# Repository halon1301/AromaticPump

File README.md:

# M5 Blowover Pump

## This device may be used in ways which can be unsafe.  I take no responsibility for unsafe usage, be smart and think with the head on your shoulders, not between your legs.
## DO NOT USE THIS DEVICE ALONE
## DO NOT USE WITH VOLATILE COMPOUNDS
## DO NOT USE WHILE INTOXICATED

Now that I've got the safety stuff done, let's get on to the fun stuff.

### Full BOM

This BOM assumes you're using the provided circuit board designs, if you're going to use strip/protoboard to build this, 
you'll need to account for the differences

| Count | Part                                         | Supplier            | Link                                                                              |
|-------|----------------------------------------------|---------------------|-----------------------------------------------------------------------------------|
| 1     | Main Circuit Board                           | PCBWay              | n/a                                                                               |
| 1     | M5Stack Core 2                               | 	DigiKey            | https://www.digikey.ca/en/products/detail/m5stack-technology-co-ltd/K010/13151126 |
| 1     | Simple RF M4 315Mhz Momentary	               | Adafruit            | https://www.adafruit.com/product/1096                                             |
| 1     | 2 Button Key Fob	                            | Adafruit	           | https://www.adafruit.com/product/1391                                             |
| 1     | 4 Button Key Fob                             | 	Adafruit	          | https://www.adafruit.com/product/1095                                             |
| 1     | 12V Pump	                                    | Amazon	             | https://a.co/d/cortGed                                                            |
| 1     | 12V 2A Power Adapter	                        | Amazon	             | https://a.co/d/3SDBTkm                                                            |
| 1     | DRV8871 DC Motor Driver(Adafruit Brand)	     | Amazon or Adafruit	 | https://www.adafruit.com/product/3190                                             |
| 1     | 7-24V to 5V Buck Converter ( RB-Dfr-956)     | RobotShop	          | https://www.robotshop.com/products/dfrobot-dc-dc-buck-converter-7-24v-to-5v-4a    |
| 1     | Barrel Plug Adapter 5.5mm                    | Amazon              | https://a.co/d/0rlC4Ci                                                            |
| 3     | 10kOhm Resistors                             | Digikey             | https://www.digikey.ca/en/products/detail/yageo/CFR-25JB-52-10K/338               |
| 3     | 22kOhm Resistors                             | DigiKey             | https://www.digikey.ca/en/products/detail/yageo/CFR-25JB-52-22K/1306              |
| 1     | Some kind of physical latching on/off switch | Amazon              | https://a.co/d/hDef00k                                                            |
| 1     | Silicone Tubing                              | Amazon              | https://a.co/d/bUvRTfo                                                            |                                                          |
| 2     | Barb Through fitting                         | Amazon              | https://a.co/d/0NNg51N                                                            |
| 2     | FPC 30 Pin boards                            | Amazon              | https://a.co/d/jerJJ3a                                                                                  |
| 1| 30 Pin ribbon cable | Amazon | https://a.co/d/dCT5ZlU                                                            |

The 4 button fob is entirely optional, as it does the same things the touchscreen on the m5stack already does.  The 2 
button remote is for a sub to use, if you don't want this, consider it optional. Only button 2 is used on the 2 button 
remote (I use button 1 for a lube pump, so it's not wired up).

There are included PCB diagrams made in KiCAD, you can get them printed with PCBWay, but this whole project could easily
be made using proto/strip board and wires.

STLs for a case are also included, these however assume you are using the PCB included with the project, please remix 
and create your own for your use case!

### Assembly
All components are through hole, this is to keep it easy for people to make on their own with basic soldering skills, 
and without requiring special PCBs or other things that may be slightly more esoteric.

The designed PCB uses standard expansion pins for most things, the connectors for the switch and the 12v to the motor 
driver are designed to use a screw block, but you really could just solder wires into the hole and call it done.  Mounting 
points on the board are designed to use M3 screws, I'd recommend a nylon washer between the screw and the board, if you 
use inserts in your case, you should probably put something on the other side, but it's mostly because I'm paranoid 
about shorts.  In my design I use a pair of breakout boards and a 30p ribbon cable to lift the M5 stack off the board 
and give me nice clearance, once again, these are optional, you could do this however you want.

If your using the provided PCB design, you'll want to use some rosin flux, it'll make your life easier.  Solder 
everything to the board where labeled.

Don't connect your M5Stack to the board when you flash it, the USB 5v is not isolated from the 5v bus, and you'll get 
weird results, or fuck your computer up.

Bring up platformIO in your IDE of choice, and run the build, then upload to your board and you are good to plug it in. 
Power up the pump, and you're ready to go.

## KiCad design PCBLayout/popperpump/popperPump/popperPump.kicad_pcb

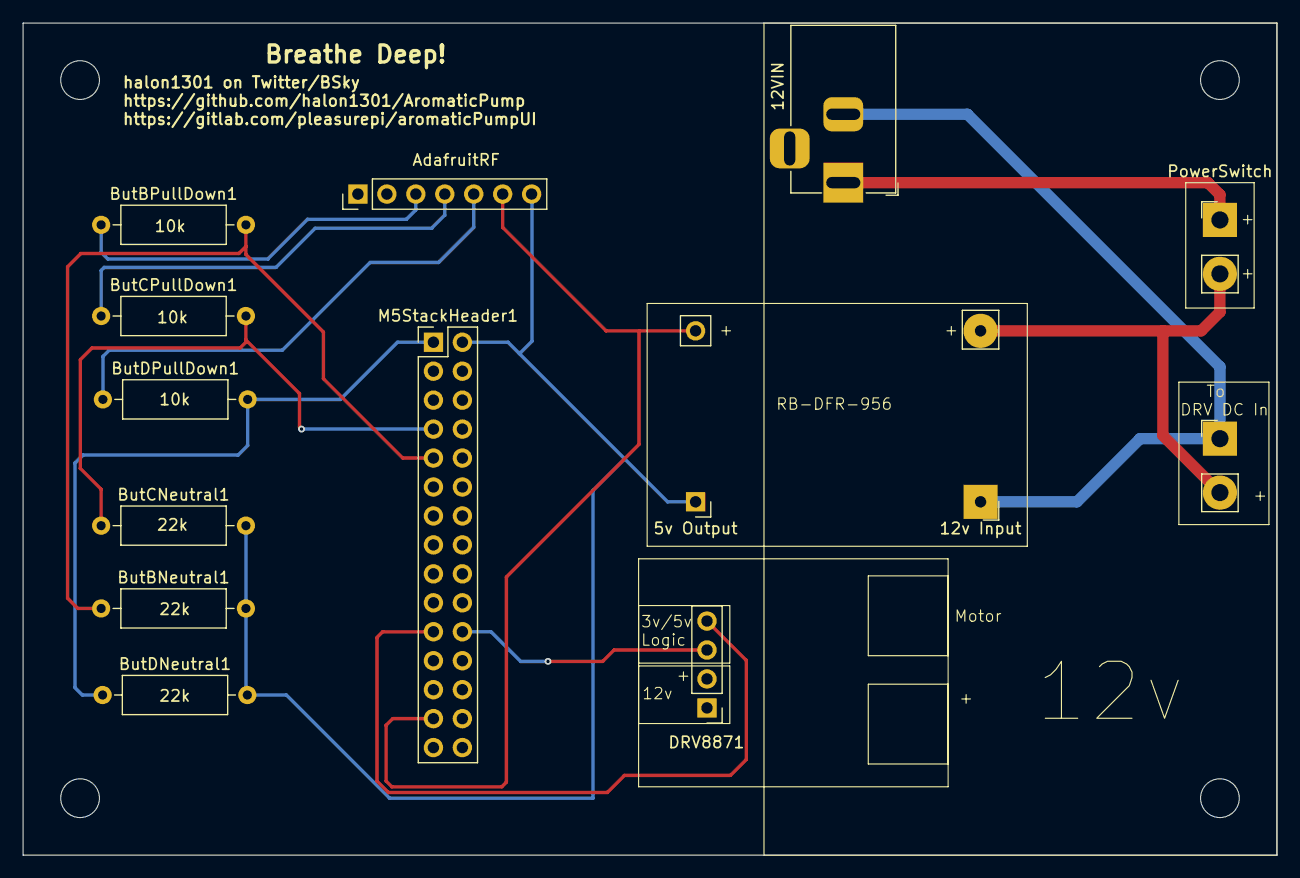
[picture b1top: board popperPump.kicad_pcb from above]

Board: 2 copper layers, 110.0 x 73.0 mm, 14 parts (0 on the bottom side), 10 nets.

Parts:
5v Output: RB-Dfr-956-5vout; PinHeader_1x02_P2.54mm_Vertical-BuckConverter-DFR-956
12VIN: Barrel_Jack; BarrelJack_Horizontal
12v Input: RB-Dfr-956-12vin; PinHeader_1x02_P2.54mm_Vertical-BuckConverter-DFR-956
AdafruitRF: Adafruit-1096; PinHeader_1x07_P2.54mm_Vertical
ButBNeutral1: 22k; R_Axial_DIN0309_L9.0mm_D3.2mm_P12.70mm_Horizontal
ButBPullDown1: 10k; R_Axial_DIN0309_L9.0mm_D3.2mm_P12.70mm_Horizontal
ButCNeutral1: 22k; R_Axial_DIN0309_L9.0mm_D3.2mm_P12.70mm_Horizontal
ButCPullDown1: 10k; R_Axial_DIN0309_L9.0mm_D3.2mm_P12.70mm_Horizontal
ButDNeutral1: 22k; R_Axial_DIN0309_L9.0mm_D3.2mm_P12.70mm_Horizontal
ButDPullDown1: 10k; R_Axial_DIN0309_L9.0mm_D3.2mm_P12.70mm_Horizontal
DRV1: DRV8871-VIN-12v; PinHeader_1x02_ForScrewBlock-1.5mmHole
DRV8871: DRV8871; PinHeader_1x04_P2.54mm_Vertical
M5StackHeader1: M5StackGPIO; PinHeader_2x15_P2.54mm_Vertical
PowerSwitch: SW_SPDT; PinHeader_1x02_ForScrewBlock-1.5mmHole

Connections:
GND: 5v Output.1, 12VIN.2, 12v Input.1, AdafruitRF.7, ButBNeutral1.2, ButCNeutral1.2, ButDNeutral1.2, DRV1.1, M5StackHeader1.2
unnamed: AdafruitRF.3, ButBPullDown1.1
unnamed: AdafruitRF.4, ButCPullDown1.1
unnamed: AdafruitRF.5, ButDPullDown1.1
unnamed: DRV8871.3, M5StackHeader1.22
unnamed: DRV8871.4, M5StackHeader1.21
unnamed: ButDNeutral1.1, ButDPullDown1.2, M5StackHeader1.1
unnamed: ButCNeutral1.1, ButCPullDown1.2, M5StackHeader1.7
unnamed: ButBNeutral1.1, ButBPullDown1.2, M5StackHeader1.9
VCC: 5v Output.2, 12VIN.1, 12v Input.2, AdafruitRF.6, M5StackHeader1.27, PowerSwitch.1 (A), PowerSwitch.2 (B)

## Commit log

2024-04-28 Adding Basic UI Elements and controls
    Adds in all the UI elements and controls for basic functionality.
2024-04-28 Working basic functionality
    On/off functions, no +10s yet.
2024-05-01 Cleanup and Remote
2024-05-02 Adds basic remote functionality
2024-05-02 Working +10s button
    NO SAFETY INTERLOCK
2024-05-05 Update Libraries
    Update lvgl to 9.0.0 and M5Unified
    Update of BOM
2024-05-06 typos
2024-05-08 Broken Commit
    This current update will not work.
    But, I'm changing my approach with the +10s idea, I think using buttons c/d on the remote and building a flow rate up/down feature is more useful than adding time.
    There's still going to be a 200s in 300s limit, or something like that, but on/off can take care of that.
2024-06-02 Big Update
    This covers all the pending changes, and pretty much solidifies v1.0 of the project.
    It is still missing all of the safety bits to take care of max run time, and x in x.
2024-06-11 2 Fixes
    - Fix the PCB layout, one of the pins was placed wrong :facepalm:
    - Remove the timing limits (coming later)
    - Update GPIO pin layout for buttons, because I'm dumb
2024-06-12 Add in a disclaimer screen
    Create an un-skippable safety disclaimer.
2024-06-15 Remove the i2c library
    I don't know how this got in here, I'm not using i2c on this project...
